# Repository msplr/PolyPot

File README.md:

# PolyPot Smart Flower Pot

PolyPot is the result of a semester project from the course *Products Design & System Engineering*.
PolyPot is a connected flower pot that automatically waters your plant and lets you monitor it's health remotely.

The microcontroller is an ESP32 and it has sensors for soil moisture, temperature, luminosity and water level connected to it.

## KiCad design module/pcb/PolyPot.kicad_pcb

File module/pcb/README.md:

# PolyPot Control Module PCB

## Issues

- Button gpio 23 does not allow wakeup from deepsleep -> connect to IO15
- Soil moisture sensor pinout is wrong. FIX THE CABLE BEFORE CONNECTING!
- IO12 is not connected to SENSOR_ENn PMOS (typo in signal name)
- IO12 must not be pulled up during boot -> use IO25
- R1 and R11 need to be ~120 Ohm to have higher LED brightness
- Footprint of buttons RESET and PROG is too small

## Images

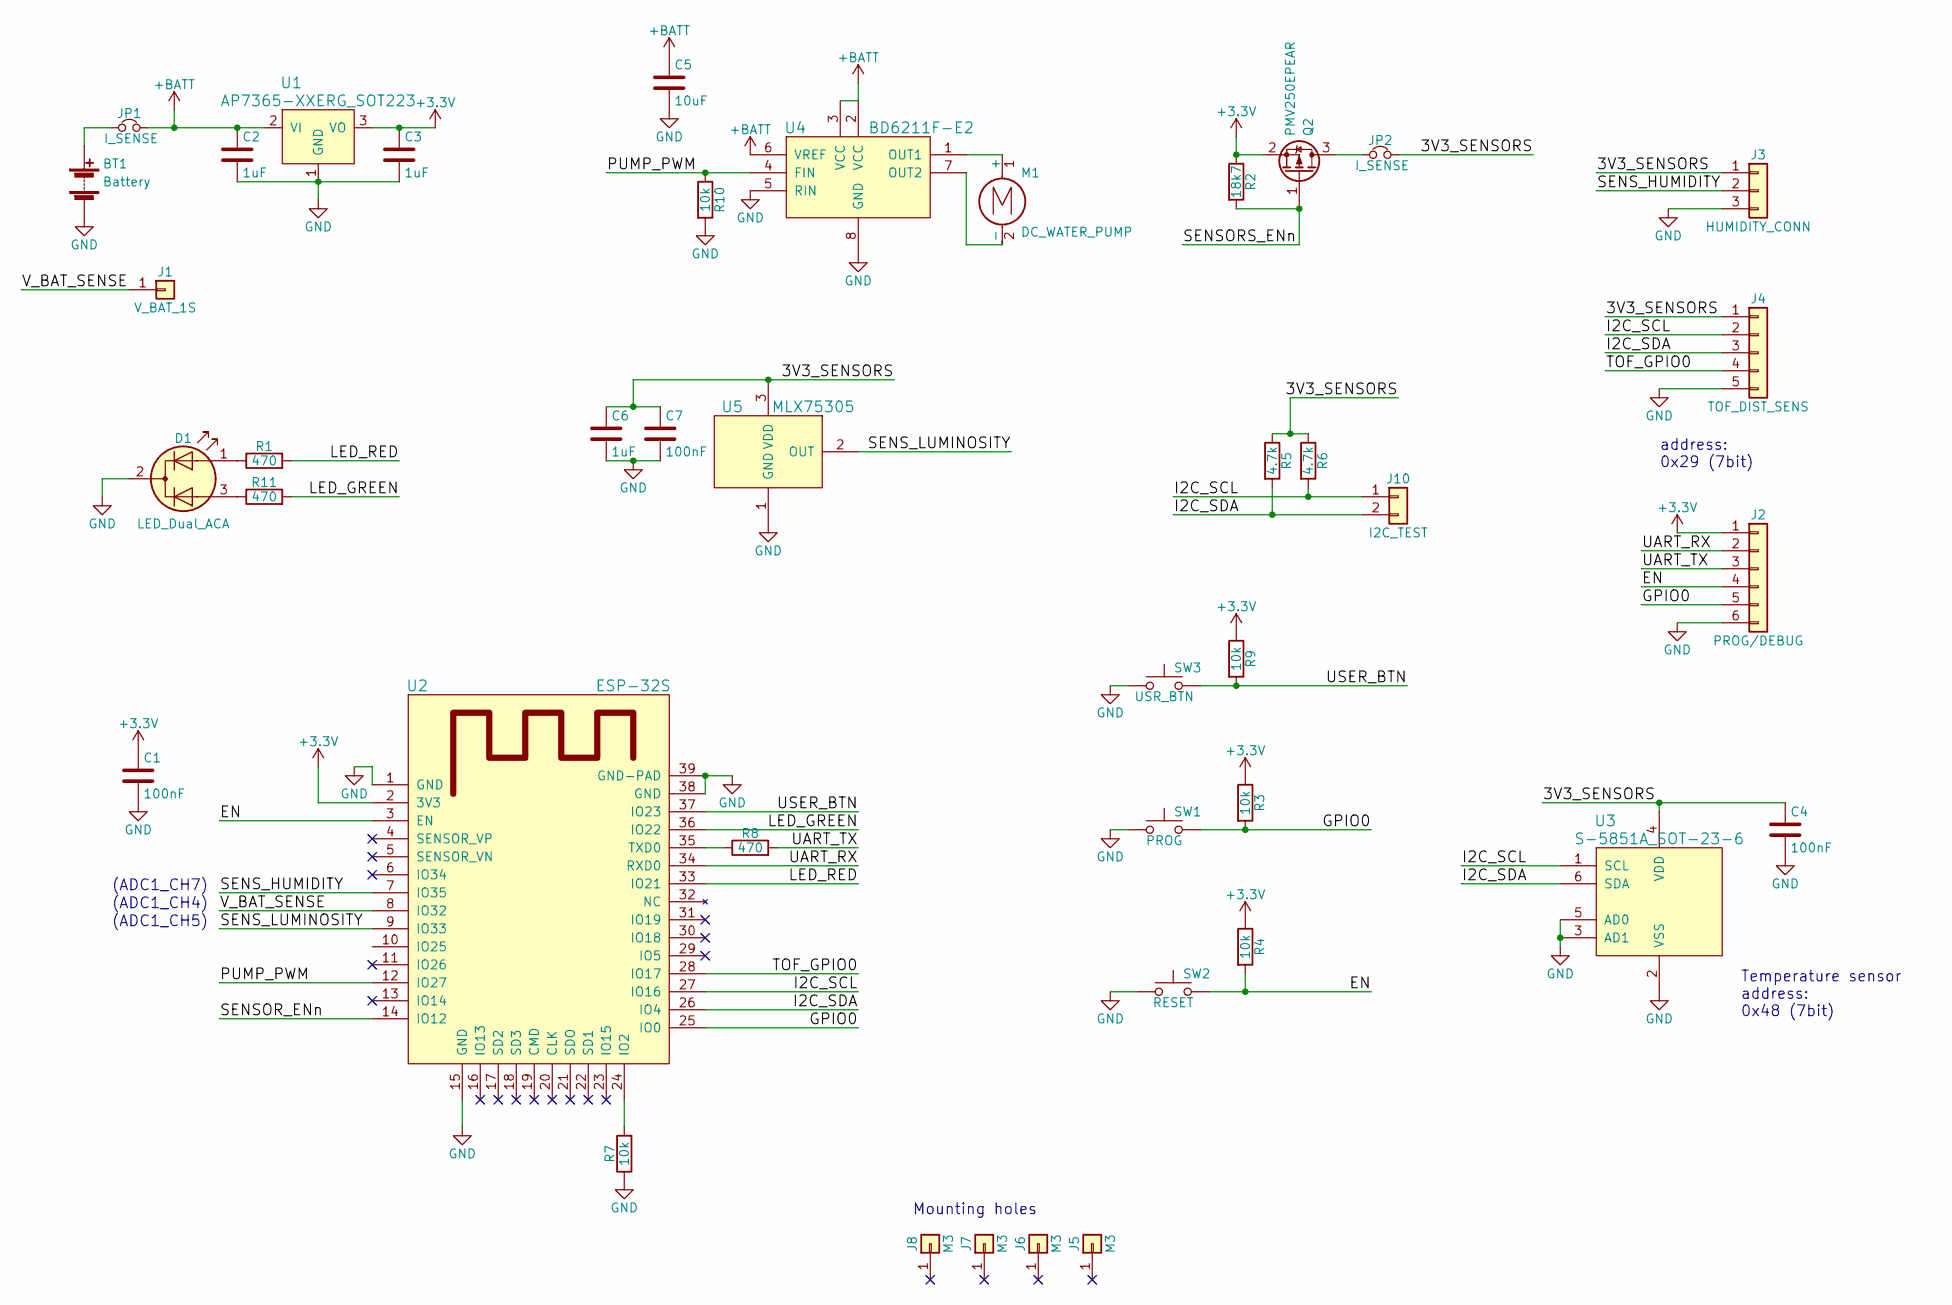
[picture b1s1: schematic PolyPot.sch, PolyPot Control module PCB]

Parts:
BT1: Battery; Pin_Header_Straight_1x02_Pitch2.54mm
C1, C4, C7: 100nF; C_0603_HandSoldering
C2, C3: 1uF; C_0603_HandSoldering
C5: 10uF; C_0805_HandSoldering
C6: 1uF; C_0805_HandSoldering
D1: LED_Dual_ACA; LED_D5.0mm-3
J1: V_BAT_1S; Pin_Header_Straight_1x01_Pitch2.54mm
J2: PROG/DEBUG; Pin_Header_Straight_1x06_Pitch2.54mm
J3: HUMIDITY_CONN; Pin_Header_Straight_1x03_Pitch2.54mm
J4: TOF_DIST_SENS; Pin_Header_Straight_1x05_Pitch2.54mm
J5, J6, J7, J8: M3; MountingHole_3.2mm_M3
J10: I2C_TEST; Pin_Header_Straight_1x02_Pitch2.54mm
JP1, JP2: I_SENSE; Pin_Header_Straight_1x02_Pitch2.54mm
M1: DC_WATER_PUMP; Pin_Header_Straight_1x02_Pitch2.54mm
Q2: PMV250EPEAR; SOT-23_Handsoldering
R1, R8, R11: 470; R_0603_HandSoldering
R2: 18k7; R_0603_HandSoldering
R3, R4, R7, R9, R10: 10k; R_0603_HandSoldering
R5, R6: 4.7k; R_0603_HandSoldering
SW1: PROG; SW_SPST_EVQPE1
SW2: RESET; SW_SPST_EVQPE1
SW3: USR_BTN; SW_SPST_PTS645
U1: AP7365-XXERG_SOT223; SOT-223
U2: ESP-32S
U3: S-5851A_SOT-23-6; SOT-23-6_Handsoldering
U4: BD6211F-E2; SOIC-8_3.9x4.9mm_Pitch1.27mm
U5: MLX75305; SOIC-8_3.9x4.9mm_Pitch1.27mm

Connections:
+3V3: C1.1, C3.1, J2.1, Q2.2 (S), R2.1, R3.1, R4.1, R9.1, U1.3 (VO), U2.2 (3V3)
+BATT: C2.1, C5.1, JP1.2, U1.2 (VI), U4.2 (VCC), U4.3 (VCC), U4.6 (VREF)
/3V3_SENSORS: C4.1, C6.1, C7.1, J3.1, J4.1, JP2.2, R5.1, R6.1, U3.4 (VDD), U5.3 (VDD)
/EN: J2.4, R4.2, SW2.2, U2.3 (EN)
/GPIO0: J2.5, R3.2, SW1.2, U2.25 (IO0)
/I2C_SCL: J4.2, J10.1, R6.2, U2.27 (IO16), U3.1 (SCL)
/I2C_SDA: J4.3, J10.2, R5.2, U2.26 (IO4), U3.6 (SDA)
/LED_GREEN: R11.2, U2.36 (IO22)
/LED_RED: R1.2, U2.33 (IO21)
/PUMP_PWM: R10.1, U2.12 (IO27), U4.4 (FIN)
/SENSORS_ENn: Q2.1 (G), R2.2
/SENS_HUMIDITY: J3.2, U2.7 (IO35)
/SENS_LUMINOSITY: U2.9 (IO33), U5.2 (OUT)
/TOF_GPIO0: J4.4, U2.28 (IO17)
/UART_RX: J2.2, U2.34 (RXD0)
/UART_TX: J2.3, R8.2
/USER_BTN: R9.2, SW3.2, U2.37 (IO23)
/V_BAT_SENSE: J1.1, U2.8 (IO32)
GND: BT1.2 (-), C1.2, C2.2, C3.2, C4.2, C5.2, C6.2, C7.2, D1.2 (K), J2.6, J3.3, J4.5, R7.1, R10.2, SW1.1, SW2.1, SW3.1, U1.1 (GND), U2.1 (GND), U2.15 (GND), U2.38 (GND), U2.39 (GND-PAD), U3.2 (VSS), U3.3 (AD1), U3.5 (AD0), U4.5 (RIN), U4.8 (GND), U5.1 (GND)
unnamed: BT1.1 (+), JP1.1
unnamed: D1.1 (A1), R1.1
unnamed: D1.3 (A2), R11.1
unnamed: JP2.1, Q2.3 (D)
unnamed: M1.1 (+), U4.1 (OUT1)
unnamed: M1.2 (-), U4.7 (OUT2)
unnamed: R7.2, U2.24 (IO2)
unnamed: R8.1, U2.35 (TXD0)

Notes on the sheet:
address: 0x29 (7bit)
Temperature sensor address: 0x48 (7bit)
Mounting holes
(ADC1_CH4)
(ADC1_CH5)
(ADC1_CH7)

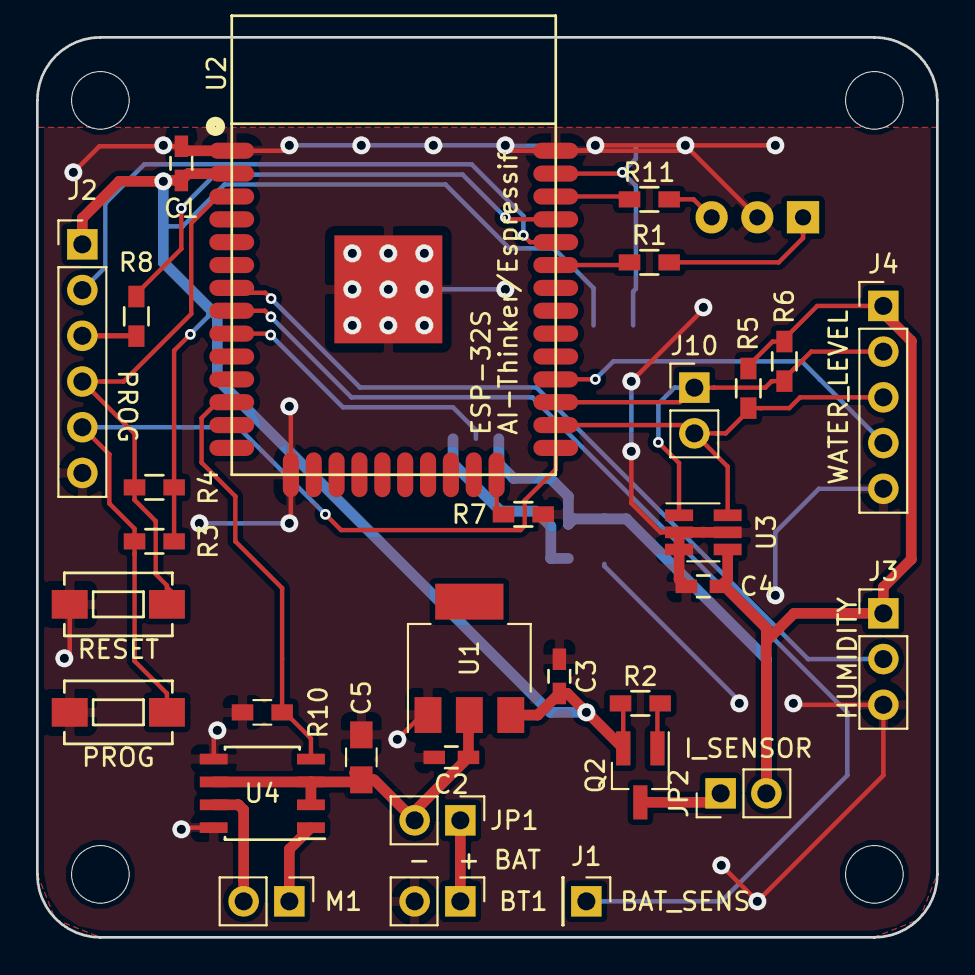
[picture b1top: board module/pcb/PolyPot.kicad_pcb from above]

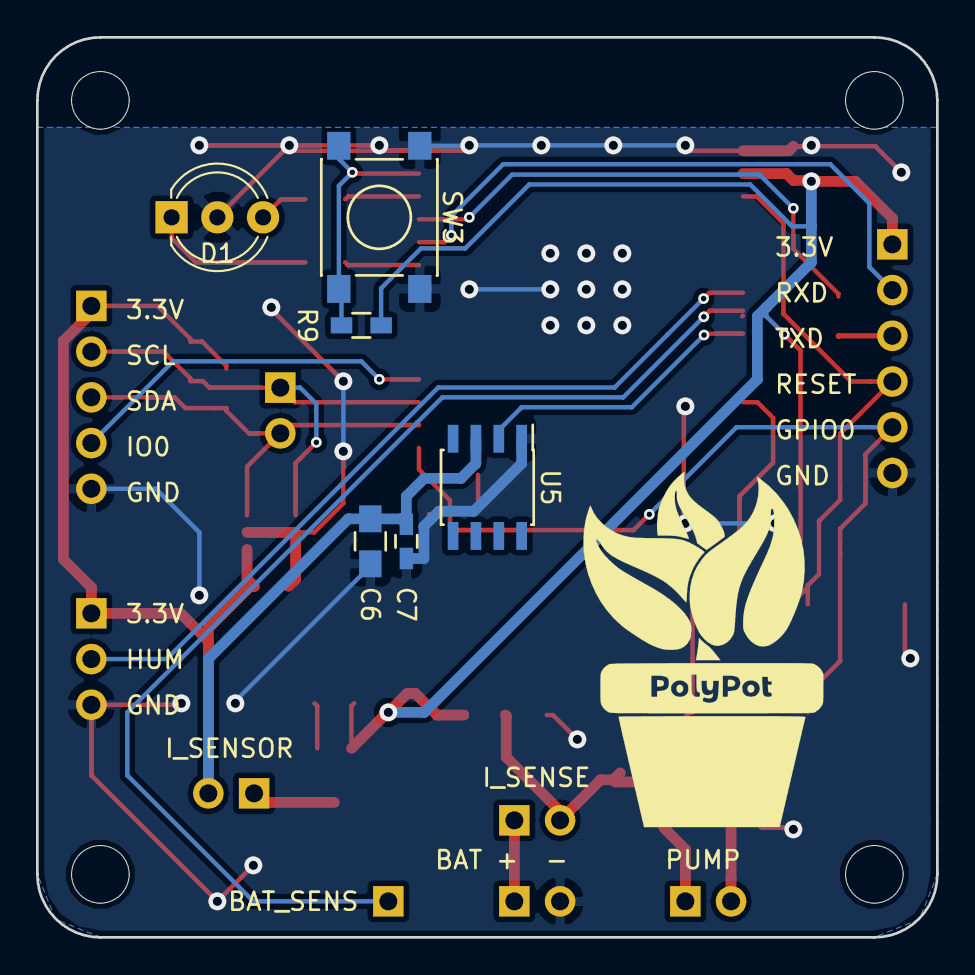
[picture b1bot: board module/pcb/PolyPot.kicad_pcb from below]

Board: 2 copper layers, 50.0 x 50.0 mm, 41 parts (6 on the bottom side), 27 nets.

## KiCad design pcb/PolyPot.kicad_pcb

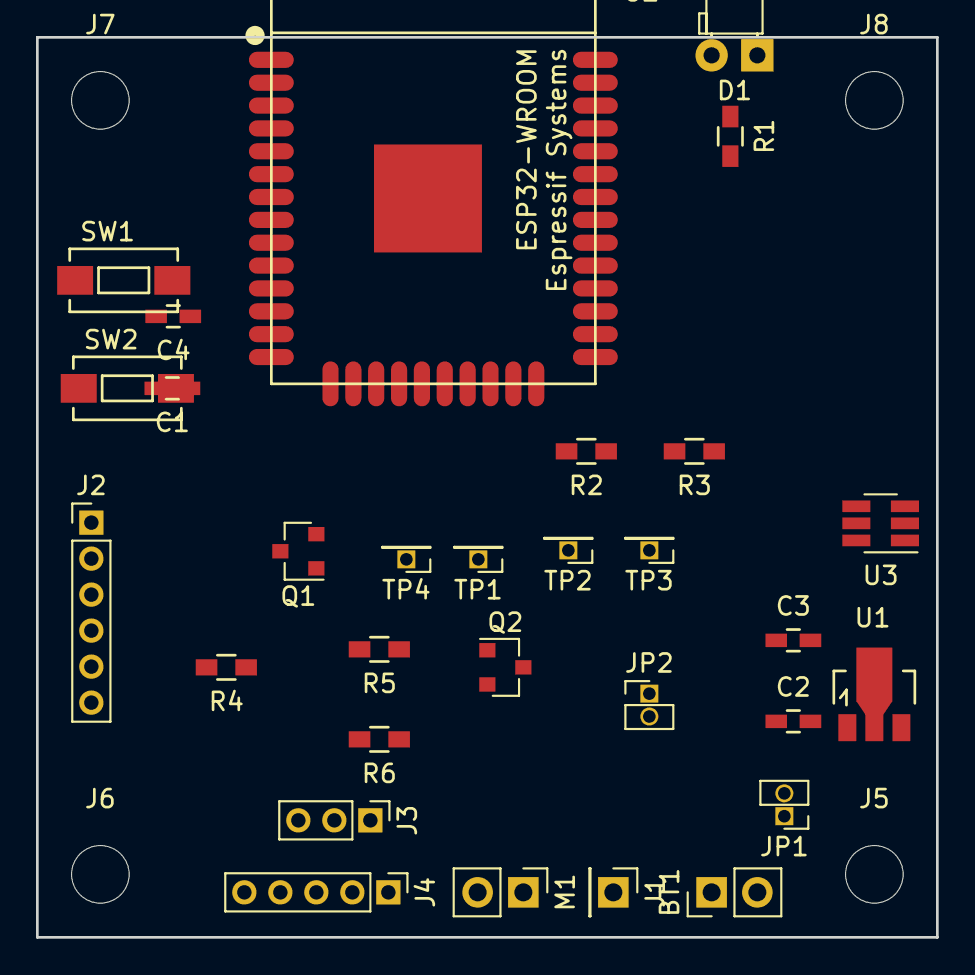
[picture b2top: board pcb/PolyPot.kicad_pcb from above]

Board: 2 copper layers, 50.0 x 50.0 mm, 34 parts (0 on the bottom side), 15 nets, no tracks yet.

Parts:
BT1: Battery; Socket_Strip_Straight_1x02_Pitch2.54mm
C1, C4: 100nF; C_0603_HandSoldering
C2, C3: 1uF; C_0603_HandSoldering
D1: LED; LED_D3.0mm_Horizontal_O1.27mm_Z2.0mm
J1: V_BAT_1S; Socket_Strip_Straight_1x01_Pitch2.54mm
J2: PROG/DEBUG; Socket_Strip_Straight_1x06_Pitch2.00mm
J3: ANALOG_CONN; Socket_Strip_Straight_1x03_Pitch2.00mm
J4: TOF_DIST_SENS; Socket_Strip_Straight_1x05_Pitch2.00mm
J5, J6, J7, J8: M3; MountingHole_3.2mm_M3
JP1, JP2: I_SENSE; Socket_Strip_Straight_1x02_Pitch1.27mm
M1: DC_WATER_PUMP; Socket_Strip_Straight_1x02_Pitch2.54mm
Q1: Q_NMOS_DGS; SOT-23
Q2: PMV250EPEAR; SOT-23
R1: 1k; R_0603_HandSoldering
R2: 18k7; R_0603_HandSoldering
R3, R4: 10k; R_0603_HandSoldering
R5, R6: 4.7k; R_0603_HandSoldering
SW1: PROG; SW_SPST_EVQPE1
SW2: RESET; SW_SPST_EVQPE1
TP1, TP2, TP3, TP4: TEST; Socket_Strip_Straight_1x01_Pitch1.27mm
U1: MCP1703A-3002_SOT89; SOT89-3_Housing
U2: ESP32-WROOM
U3: S-5851A_SOT-23-6; SOT-23-6_Handsoldering

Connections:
+3V3: C1.1, C3.1, J2.1, Q2.2, R2.1, R3.1, R4.1, U1.3, U2.2
/3V3_SENSORS: C4.1, J3.1, J4.1, JP2.2, R5.1, R6.1, U3.4
/EN: J2.4, R4.2, SW2.2, TP4.1, U2.3
/GPIO0: J2.5, R3.2, SW1.2, TP3.1, U2.25
/I2C_SCL: J4.2, R6.2, TP2.1, U3.1
/I2C_SDA: J4.3, R5.2, TP1.1, U3.6
/SENSORS_ENn: Q2.1, R2.2
/UART_RX: J2.2, U2.34
/UART_TX: J2.3, U2.35
GND: BT1.2, C1.2, C2.2, C3.2, C4.2, J2.6, J3.3, J4.5, Q1.3, R1.2, SW1.1, SW2.1, U1.1, U3.2, U3.3, U3.5
unnamed: BT1.1, JP1.1
unnamed: C2.1, JP1.2, U1.2
unnamed: D1.1, R1.1
unnamed: JP2.1, Q2.3
unnamed: M1.2, Q1.1

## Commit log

2017-11-05 Start working on schematic
2017-11-05 README
2017-11-09 Add temperature sensor, V_Bat sense
2017-11-09 Component annotation
2017-11-09 Assign footprints, start with PCB
2017-11-09 Add ESP32 3d shape
2017-11-09 PCB: rough component placement
2017-11-10 Move files related to the module in their own directory
2017-11-10 First version of the communication protocol with example files and generation script
2017-11-10 Start server development. Can only manage raw data currently.
2017-11-11 Add the configuration to content sent to the smartphone and precise that time is UTC time
2017-11-11 Update and reword protocol
2017-11-11 Add command and configuration support to server, update server to current protocol
2017-11-14 Update pin assignment, add user button, add luminosity conn
2017-11-16 PCB: update voltage regulator
2017-11-16 PCB: updtate local lib
2017-11-16 PCB: 3d model placement
2017-11-16 New protocol version using UUID and covering setup
2017-11-16 Update server to use UUID and add homepage
2017-11-16 Add logo material
2017-11-17 First PCB routage+ small correction int the schematics
2017-11-17 PCB routage (except for track width to modify)
2017-11-17 Slightly better database model to store configuration
2017-11-19 Add ability to limit data returned by server
2017-11-19 Logo with transparent background
2017-11-19 Progress on website design
2017-11-20 Minor correction in the schematics
    User_Button was improperly connected. There were two signals (user_button and user_btn) not linked to each other
2017-11-20 Updated track width
2017-11-20 Adding footprint and schematics for esp32-s
    This is a GitHub library containing the Ki-Cad schematics and footprints for ESP-32 S, ESP-32-WROOM and ESP32. It also contaains the datasheets necessary to check the pin assignment and wiring.
2017-11-20 Replaced ESP32-WROOM with ESP32-S
2017-11-20 New routing using the ESP32-S footprint
2017-11-21 Added the PWM driver and routed it on the PCB
    There might be some issues with the path for library for ESP32-S. You might need to respecify the path to "ESP32-footprints-Lib.pretty" in the PCB editor library manager.
2017-11-23 PCB: Update footprints, schematic fixes, nicer edge cut, no GND next to antenna
2017-11-23 PCB: change SOIC-8 footprint
2017-11-23 Add logo
2017-11-24 PCB: fix 3.3V regulator footprint, connect TOF GPIO0, start routing
2017-11-24 PCB: routing almost done, silkscreen text
2017-11-24 PCB: ground connection vias
2017-11-24 Move logo and add icons
2017-11-24 Add mechanical design
2017-11-25 PCB: new routing with luminosity sensor, move LED and button to upper side.
2017-11-25 PCB: add luminosity sensor to schematic
2017-11-25 Add smartphone app (mostly design)
2017-11-25 added functions
2017-11-25 PCB: add dimension drawings
2017-11-25 minor changes
2017-11-25 Add PreferenceString + default values
2017-11-25 Empty summary by default
2017-11-25 PCB: gerber files
2017-11-25 PCB: improve GND connection
2017-11-25 Correct code in CommunicationManager and Summary
2017-11-25 PCB: add images
2017-11-25 PCB: schematic pdf
2017-11-25 PCB: datasheets
2017-11-25 PCB: dimensions drawing
2017-11-26 Use tab name instead of using number, error message if an error occurred, new design using callbacks
2017-11-26 Start working on graphs
2017-11-26 Nomenclature uniformisation
2017-11-26 Show value in PreferenceSeekBarDialog, change graph library, implement graph support
2017-11-26 Resolve bugs when switching between tabs, rotating and due to timezone handling
2017-11-26 De-duplicate graph code
2017-11-26 Convert Date and Time management to java API (instead of android)
2017-11-26 Correct LID and add assembly
2017-11-26 Fully support rotating screen
2017-11-26 Fix a bunch of warnings and errors
2017-11-27 Small improvements on charts, handle back button, better CommunicationManager + use directly JsonObjectRequest
2017-11-29 Add full support for configuration, rewrite CM and move to EventBus, add fadded icon for tabs
2017-11-30 Color adjustment, change configuration icon, resolve bug with CM, prepare for release
2017-12-02 Add Setup support
2017-12-02 Fix warnings, better internationalization
2017-12-02 Update server and protocol
2017-12-02 Add commands support and better error handling
2017-12-02 Mutualize dimensions and better internationalization
2017-12-03 Add "Water plant" button, fix setup, add possibility to add a hint in CM Request, use ressources for all dates
2017-12-04 PCB README
2017-12-07 Multi pot support, rework setup, settings and CM, start adding plant tab
2017-12-09 Creating sourcecode file
    Source code for esp32
2017-12-09 Add weekly and monthly graph, add possibility to refresh, add limit for target moisture, start adding plants database support, support config rollback
2017-12-09 module: add test scripts
2017-12-09 More PCB bugs
2017-12-09 Update hardware fixes in schematic
2017-12-09 Sensors and LED test scripts, update io pins
2017-12-09 temperature sensor test
2017-12-09 set moisture sensor gain, TOF sensor enable
2017-12-10 Start working on TOF distance sensor driver
2017-12-10 PCB: Comment about button footprint
2017-12-10 Update protocol (with server and smartphone) + fix bug with ConfigurationSnackbar
2017-12-14 Ugraded network, almost finished main.
2017-12-14 Validated setup
2017-12-14 Updated main
2017-12-14 Corrected minor bug and typos
2017-12-14 Fixed the ntptime
    Should be still checked with a wifi connection
2017-12-14 Add stats, plant database and plant status support, add background color to pot icons, add notifications, general rework
2017-12-15 working TOF senosr driver
2017-12-15 test TOF sensor notes
2017-12-15 refactor pin initialization
2017-12-15 pump module
2017-12-15 test TOF sensor driver
2017-12-15 update LED module
2017-12-15 put everythin in board and sensors module
2017-12-15 bug fixes
2017-12-15 Add module and update assembly
2017-12-15 Import urequests
2017-12-15 remove pin initialization, import board
2017-12-15 changes by loic
2017-12-15 Better connect protocol, fixed serveer com bug
2017-12-15 Add sensors readout
2017-12-15 pwm problems, switch to all/nothin pump control
2017-12-15 Deleted debug prints
2017-12-15 Add solidworks rendering
2017-12-15 implemented commends type support
2017-12-15 Started to work on commands
2017-12-15 Finished simple command managment
2017-12-15 Correcting sensor start
2017-12-15 TOF calibration
2017-12-15 typo in com
2017-12-15 static wifi setup test
2017-12-15 typo
2017-12-15 typos
2017-12-15 debugging
2017-12-15 Cleaned and debbuged
2017-12-15 Debbuged, and started cleaning
2017-12-15 Cleaning the code and adding some functions
    Some more functions were made to help modular programmtion
2017-12-15 Cleaning code+use new functions from communication
2017-12-16 Fixed ntptime offset
    Fixed the 30 years offset given by standard ntptime by adding a embeded_ntptime which took this into account
2017-12-16 Fixed minor typos in functions names
2017-12-16 Fixed minor bug with settime
2017-12-17 Pictures
2017-12-17 Transparent background for all images
2017-12-18 Aloows to write in flash memory
2017-12-18 Woops wrong place
2017-12-18 Alows to write varibales in flash memory
    Module was tested and works on the esp32
2017-12-18 Added some error management
    Impoemeted the handeling of various connection errors
2017-12-18 Changed the wlan/ap handeling
    Chnaged the behaviour of the functions hadeling wlan and ap (added some del()) in order to have less data to store when going in deepsleep.
2017-12-18 Started to implement permanent memory
2017-12-18 Finished non volatile memory
    Still requires testing
2017-12-18 Added LED
    LED is red if module is awake and not setup
    LED is green if module is awake and setup
    LED is off when module sleeps
2017-12-18 Better LED managment
    GREEN: all works fine
    ORANGE: try to connect
    RED: waiting for configuration or connection failed
2017-12-18 Implemented server communication errors
2017-12-19 module debugging, use dummy config
2017-12-19 Minor big fix
2017-12-19 Added some correction factors
2017-12-21 Over-protecting the code
    Implementing an over protected version of the code in order to have a stable module at the presentation. No consideation for the computational cost
2017-12-21 Fixed minor bugs, implemented fatal error
    Fatal error is implemented with a master try catch
2017-12-21 Added some debug prints
2017-12-22 added some moke values and came back to earlier version
2017-12-22 Fixed minor bug
    Working code
2017-12-22 IMPORTANT: corrected syntax
2017-12-22 Corrected water vollume
    added a few lines to adapte the watering time
2017-12-22 Screenshots and features of app
2017-12-22 Add ads and about screen, better error management
2017-12-22 Add solidworks rendering (Work by Guillaume)
2017-12-22 Add videos
2017-12-25 Few adjustments
    Mostly easthetic adjusments. Plus chaged a few errors to have a more consistant error handeling
